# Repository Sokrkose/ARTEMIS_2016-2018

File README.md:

# Applied Research Team in Electronics & Microcontrolled Systems (ARTEMIS)

Some projects that I developed in the University Research Team ARTEMIS, while I was member of the team (2016-2018)

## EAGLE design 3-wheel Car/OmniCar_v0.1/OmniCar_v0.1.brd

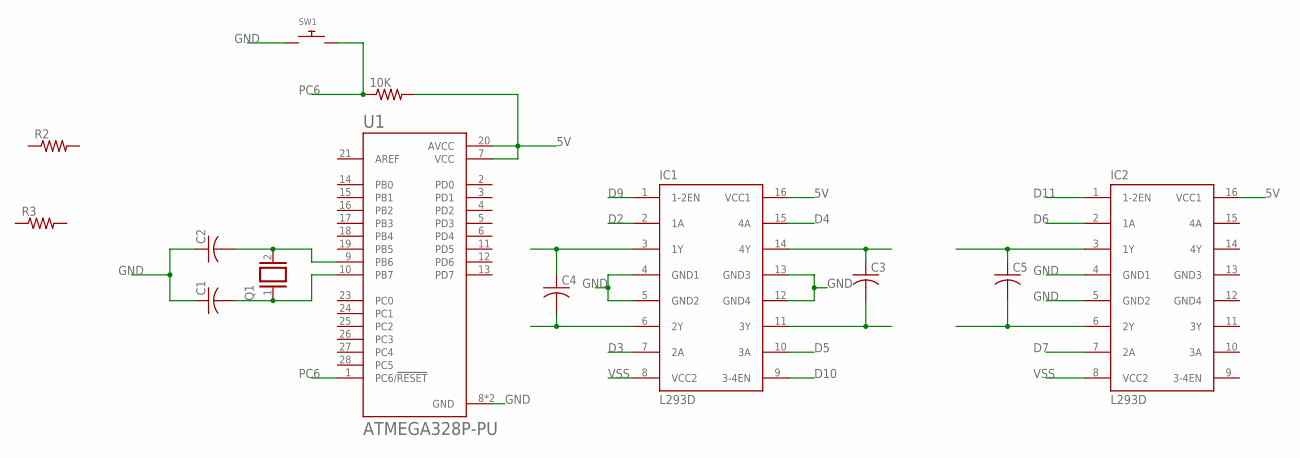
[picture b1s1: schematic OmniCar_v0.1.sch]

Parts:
10K: R-US_0204/5; 0204/5
C1, C2, C3, C4, C5: C-US025-030X050; C025-030X050
IC1, IC2: L293D; DIL16
Q1: XTAL; Q
R2, R3: R-US_0204/5; 0204/5
SW1: SWITCH_PUSHBUTTONEVQ-PE; TACT_PANA-EVQ
U1: ATMEGA328P-PU; DIP794W46P254L2967H457Q28B

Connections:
5V: 10K.2, IC1.16 (VCC1), IC2.16 (VCC1), U1.7 (VCC), U1.20 (AVCC)
D2: IC1.2 (1A)
D3: IC1.7 (2A)
D4: IC1.15 (4A)
D5: IC1.10 (3A)
D6: IC2.2 (1A)
D7: IC2.7 (2A)
D9: IC1.1 (1-2EN)
D10: IC1.9 (3-4EN)
D11: IC2.1 (1-2EN)
GND: C1.1, C2.1, IC1.4 (GND1), IC1.5 (GND2), IC1.12 (GND4), IC1.13 (GND3), IC2.4 (GND1), IC2.5 (GND2), SW1.P$1, U1.8 (GND), U1.22 (GND)
GND3: IC2.13 (GND3)
GND4: IC2.12 (GND4)
unnamed: C2.2, Q1.2, U1.9 (PB6)
unnamed: C1.2, Q1.1, U1.10 (PB7)
unnamed: C4.1, IC1.3 (1Y)
unnamed: C4.2, IC1.6 (2Y)
unnamed: C3.1, IC1.14 (4Y)
unnamed: C3.2, IC1.11 (3Y)
unnamed: C5.1, IC2.3 (1Y)
unnamed: C5.2, IC2.6 (2Y)
PC6: 10K.1, SW1.P$2, U1.1 (PC6/!RESET)
VSS: IC1.8 (VCC2), IC2.8 (VCC2)

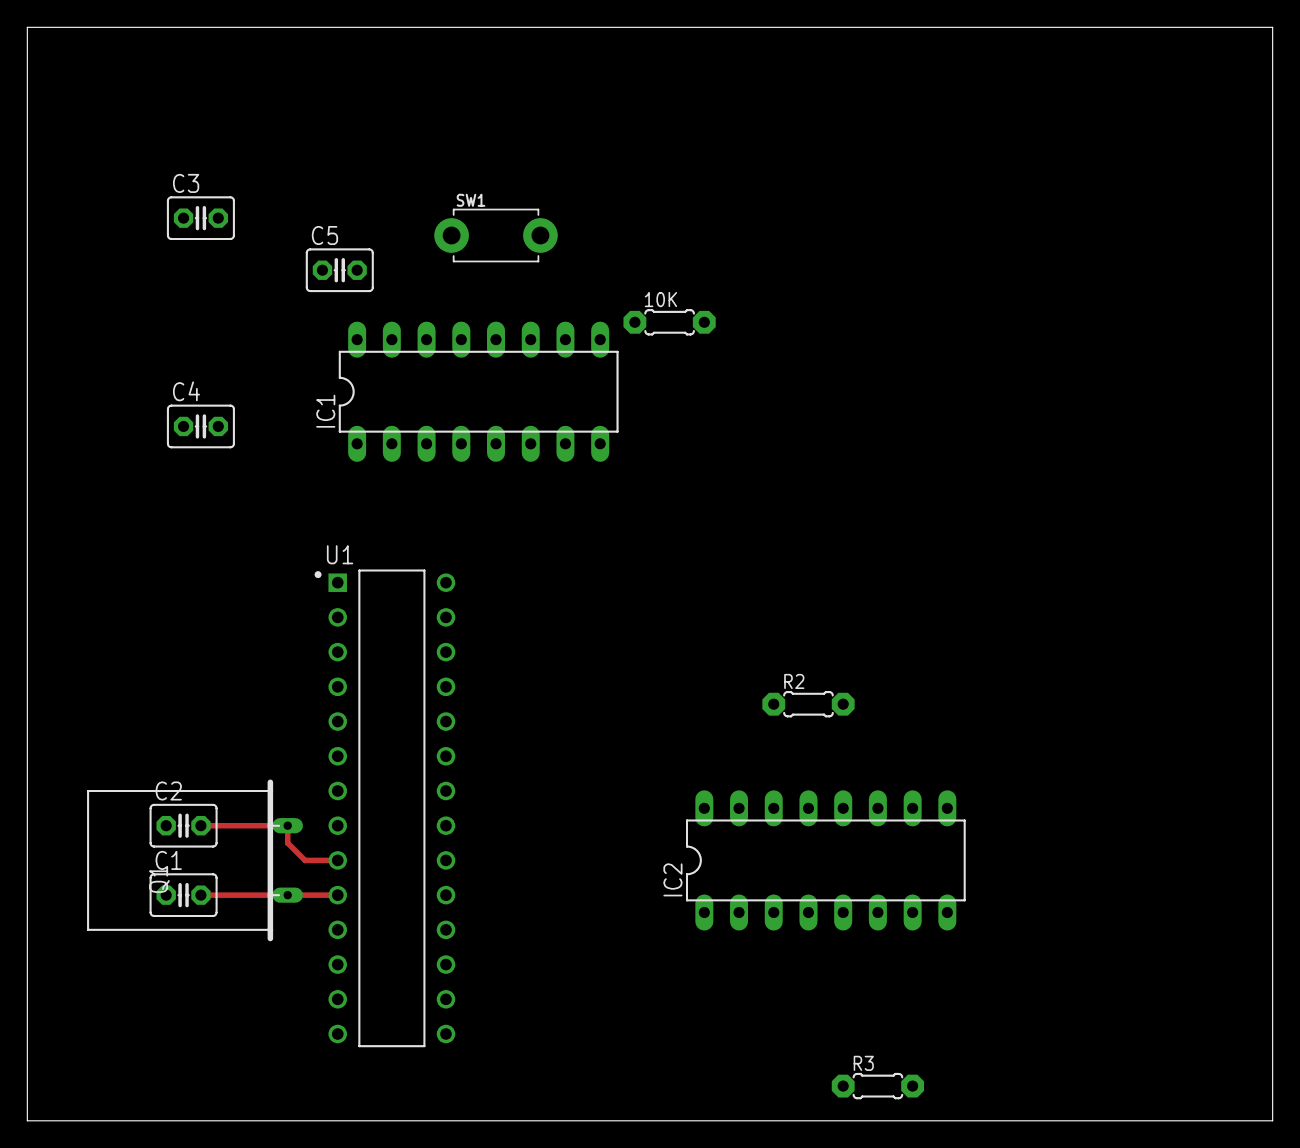
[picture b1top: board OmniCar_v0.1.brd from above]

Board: 2 copper layers, 91.1 x 80.0 mm, 13 parts (0 on the bottom side), 12 nets.

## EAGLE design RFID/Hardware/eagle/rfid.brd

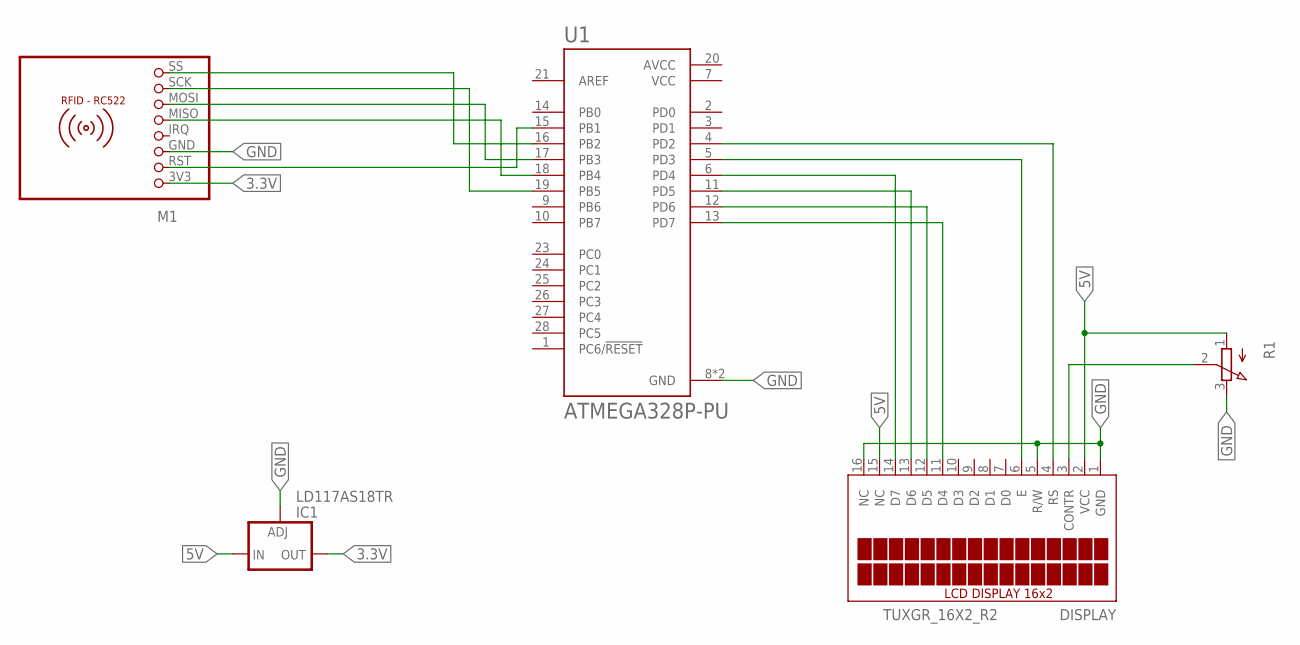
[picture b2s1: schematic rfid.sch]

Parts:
DISPLAY: TUXGR_16X2_R2
IC1: LD117AS18TR; SOT223
M1: RFID-RC522
R1: 3RP/1610N
U1: ATMEGA328P-PU; DIP794W46P254L2967H457Q28B

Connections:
3.3V: IC1.4 (OUT), M1.3V3 (1)
5V: DISPLAY.2 (VCC), IC1.3 (IN), R1.1 (A)
AVCC: U1.20 (AVCC)
GND: DISPLAY.1 (GND), DISPLAY.5 (R/W), DISPLAY.16 (NC), IC1.1 (ADJ), M1.GND (3), R1.3 (E), U1.8 (GND), U1.22 (GND)
unnamed: M1.RST (2), U1.15 (PB1)
unnamed: M1.MISO (5), U1.18 (PB4)
unnamed: M1.MOSI (6), U1.17 (PB3)
unnamed: M1.SCK (7), U1.19 (PB5)
unnamed: M1.SS (8), U1.16 (PB2)
unnamed: DISPLAY.3 (CONTR), R1.2 (S)
unnamed: DISPLAY.4 (RS), U1.4 (PD2)
unnamed: DISPLAY.6 (E), U1.5 (PD3)
unnamed: DISPLAY.11 (D4), U1.13 (PD7)
unnamed: DISPLAY.12 (D5), U1.12 (PD6)
unnamed: DISPLAY.13 (D6), U1.11 (PD5)
unnamed: DISPLAY.14 (D7), U1.6 (PD4)
VCC: U1.7 (VCC)

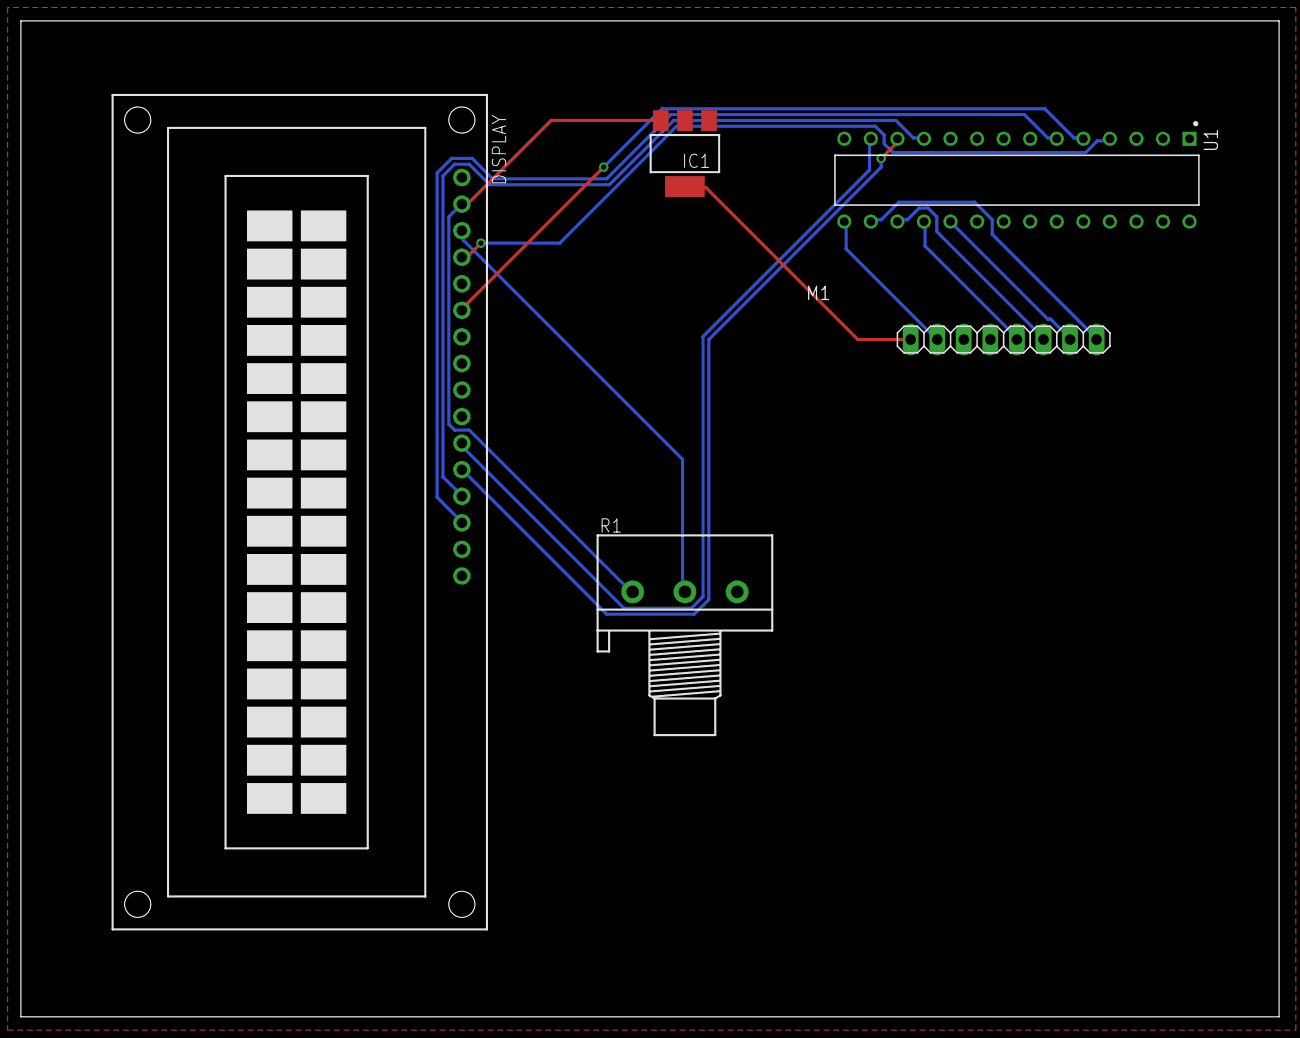
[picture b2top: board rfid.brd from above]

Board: 2 copper layers, 120.3 x 95.2 mm, 5 parts (0 on the bottom side), 15 nets.

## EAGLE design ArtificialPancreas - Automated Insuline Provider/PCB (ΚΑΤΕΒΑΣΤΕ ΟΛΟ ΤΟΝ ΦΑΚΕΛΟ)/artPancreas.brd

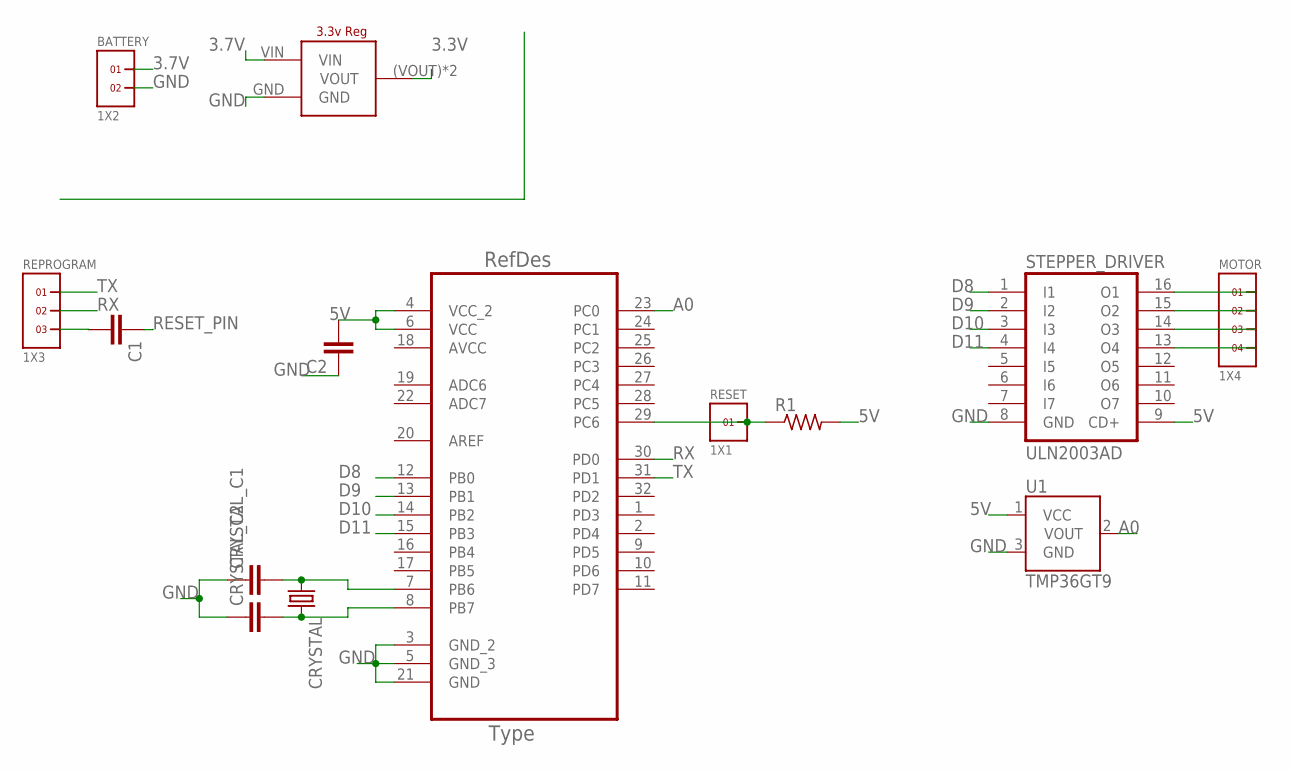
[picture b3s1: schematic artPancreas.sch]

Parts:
ATMEGA328SMD: ATMEGA328P-AU; QFP80P900X900X120-32N
BATTERY: 1X2
C1, C2: C2,5-3; C2.5-3
CRYSTAL: CRYSTALHC18U-V; HC18U-V
CRYSTAL_C1, CRYSTAL_C2: C2,5-3; C2.5-3
MOTOR: 1X4
R1: R-US_0204/5; 0204/5
REPROGRAM: 1X3
RESET: 1X1
STEPPER_DRIVER: ULN2003AD; SO16
U1: TMP36GT9; TO-92
U$1: LD1117; LD1117SOT-223

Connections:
3.3V: U$1.(VOUT) (VOUT), U$1.VOUT
3.7V: BATTERY.1, U$1.VIN
5V: ATMEGA328SMD.4 (VCC_2), ATMEGA328SMD.6 (VCC), C2.2, R1.2, STEPPER_DRIVER.9 (CD+), U1.1 (VCC)
A0: ATMEGA328SMD.23 (PC0), U1.2 (VOUT)
AVCC: ATMEGA328SMD.18 (AVCC)
D8: ATMEGA328SMD.12 (PB0), STEPPER_DRIVER.1 (I1)
D9: ATMEGA328SMD.13 (PB1), STEPPER_DRIVER.2 (I2)
D10: ATMEGA328SMD.14 (PB2), STEPPER_DRIVER.3 (I3)
D11: ATMEGA328SMD.15 (PB3), STEPPER_DRIVER.4 (I4)
GND: ATMEGA328SMD.3 (GND_2), ATMEGA328SMD.5 (GND_3), ATMEGA328SMD.21 (GND), BATTERY.2, C2.1, CRYSTAL_C1.1, CRYSTAL_C2.1, STEPPER_DRIVER.8 (GND), U1.3 (GND), U$1.GND
unnamed: ATMEGA328SMD.7 (PB6), CRYSTAL.1, CRYSTAL_C1.2
unnamed: ATMEGA328SMD.8 (PB7), CRYSTAL.2, CRYSTAL_C2.2
unnamed: MOTOR.1, STEPPER_DRIVER.16 (O1)
unnamed: MOTOR.2, STEPPER_DRIVER.15 (O2)
unnamed: C1.2, REPROGRAM.3
unnamed: MOTOR.3, STEPPER_DRIVER.14 (O3)
unnamed: MOTOR.4, STEPPER_DRIVER.13 (O4)
RESET_PIN: ATMEGA328SMD.29 (PC6), C1.1, R1.1, RESET.1
RX: ATMEGA328SMD.30 (PD0), REPROGRAM.2
TX: ATMEGA328SMD.31 (PD1), REPROGRAM.1

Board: 2 copper layers, 14 parts (0 on the bottom side), 19 nets, no tracks yet.

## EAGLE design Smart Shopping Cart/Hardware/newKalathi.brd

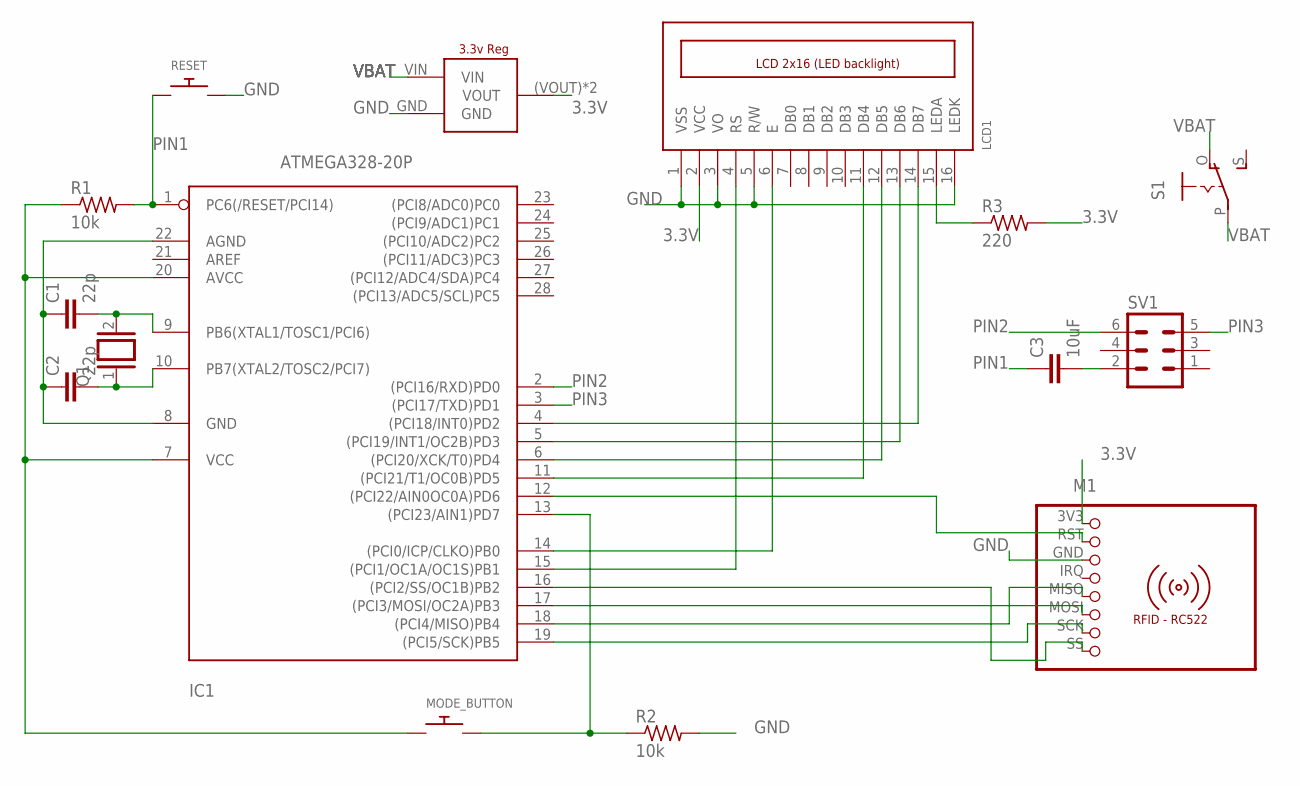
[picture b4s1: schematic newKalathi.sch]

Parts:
C1, C2: 22p; C2.5-3
C3: 10uF; C5B3
IC1: ATMEGA328-20P; DIL28-3
LCD1: LCD_2X16_SIL; HY-1602F
M1: RFID-RC522
MODE_BUTTON: SWITCH_PUSHBUTTONEVQ-PE; TACT_PANA-EVQ
Q1: XTAL; Q
R1, R2: 10k; 0204/7
R3: 220; 0204/7
RESET: SWITCH_PUSHBUTTONEVQ-PE; TACT_PANA-EVQ
S1: EG1218S; EG1218
SV1: MA03-2
U$1: LD1117; LD1117SOT-223

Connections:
3.3V: IC1.7 (VCC), IC1.20 (AVCC), LCD1.2 (VCC), M1.3V3 (1), MODE_BUTTON.P$1, R1.1, R3.2, U$1.(VOUT) (VOUT), U$1.VOUT
GND: C1.1, C2.1, IC1.8 (GND), IC1.22 (AGND), LCD1.1 (VSS), LCD1.3 (VO), LCD1.5 (R/W), LCD1.16 (LEDK), M1.GND (3), R2.2, RESET.P$2, U$1.GND
unnamed: IC1.17 ((PCI3/MOSI/OC2A)PB3), M1.MOSI (6)
unnamed: IC1.18 ((PCI4/MISO)PB4), M1.MISO (5)
unnamed: IC1.19 ((PCI5/SCK)PB5), M1.SCK (7)
unnamed: IC1.11 ((PCI21/T1/OC0B)PD5), LCD1.11 (DB4)
unnamed: IC1.13 ((PCI23/AIN1)PD7), MODE_BUTTON.P$2, R2.1
unnamed: IC1.16 ((PCI2/SS/OC1B)PB2), M1.SS (8)
unnamed: IC1.12 ((PCI22/AIN0OC0A)PD6), M1.RST (2)
unnamed: IC1.4 ((PCI18/INT0)PD2), LCD1.14 (DB7)
unnamed: IC1.5 ((PCI19/INT1/OC2B)PD3), LCD1.13 (DB6)
unnamed: IC1.6 ((PCI20/XCK/T0)PD4), LCD1.12 (DB5)
unnamed: IC1.14 ((PCI0/ICP/CLKO)PB0), LCD1.6 (E)
unnamed: IC1.15 ((PCI1/OC1A/OC1S)PB1), LCD1.4 (RS)
unnamed: LCD1.15 (LEDA), R3.1
unnamed: C1.2, IC1.9 (PB6(XTAL1/TOSC1/PCI6)), Q1.2
unnamed: C2.2, IC1.10 (PB7(XTAL2/TOSC2/PCI7)), Q1.1
unnamed: C3.2, SV1.2
PIN1: C3.1, IC1.1 (PC6(/RESET/PCI14)), R1.2, RESET.P$1
PIN2: IC1.2 ((PCI16/RXD)PD0), SV1.6
PIN3: IC1.3 ((PCI17/TXD)PD1), SV1.5
VBAT: S1.O, S1.P, U$1.VIN

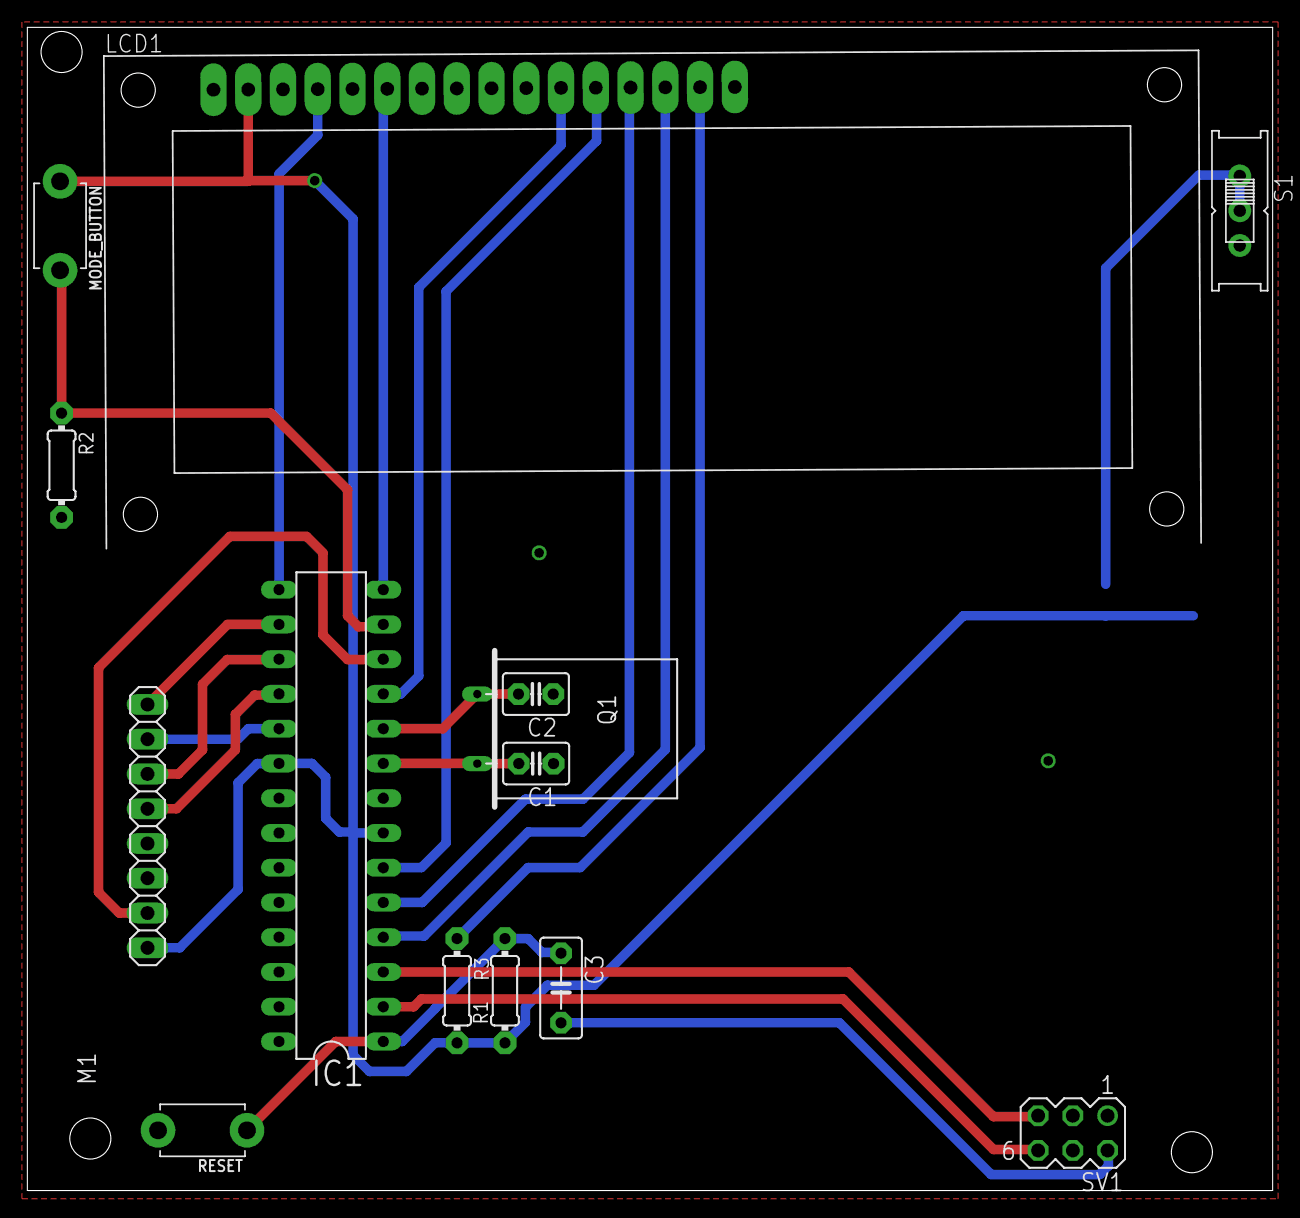
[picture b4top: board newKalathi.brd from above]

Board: 2 copper layers, 91.0 x 85.0 mm, 15 parts (1 on the bottom side), 22 nets.
